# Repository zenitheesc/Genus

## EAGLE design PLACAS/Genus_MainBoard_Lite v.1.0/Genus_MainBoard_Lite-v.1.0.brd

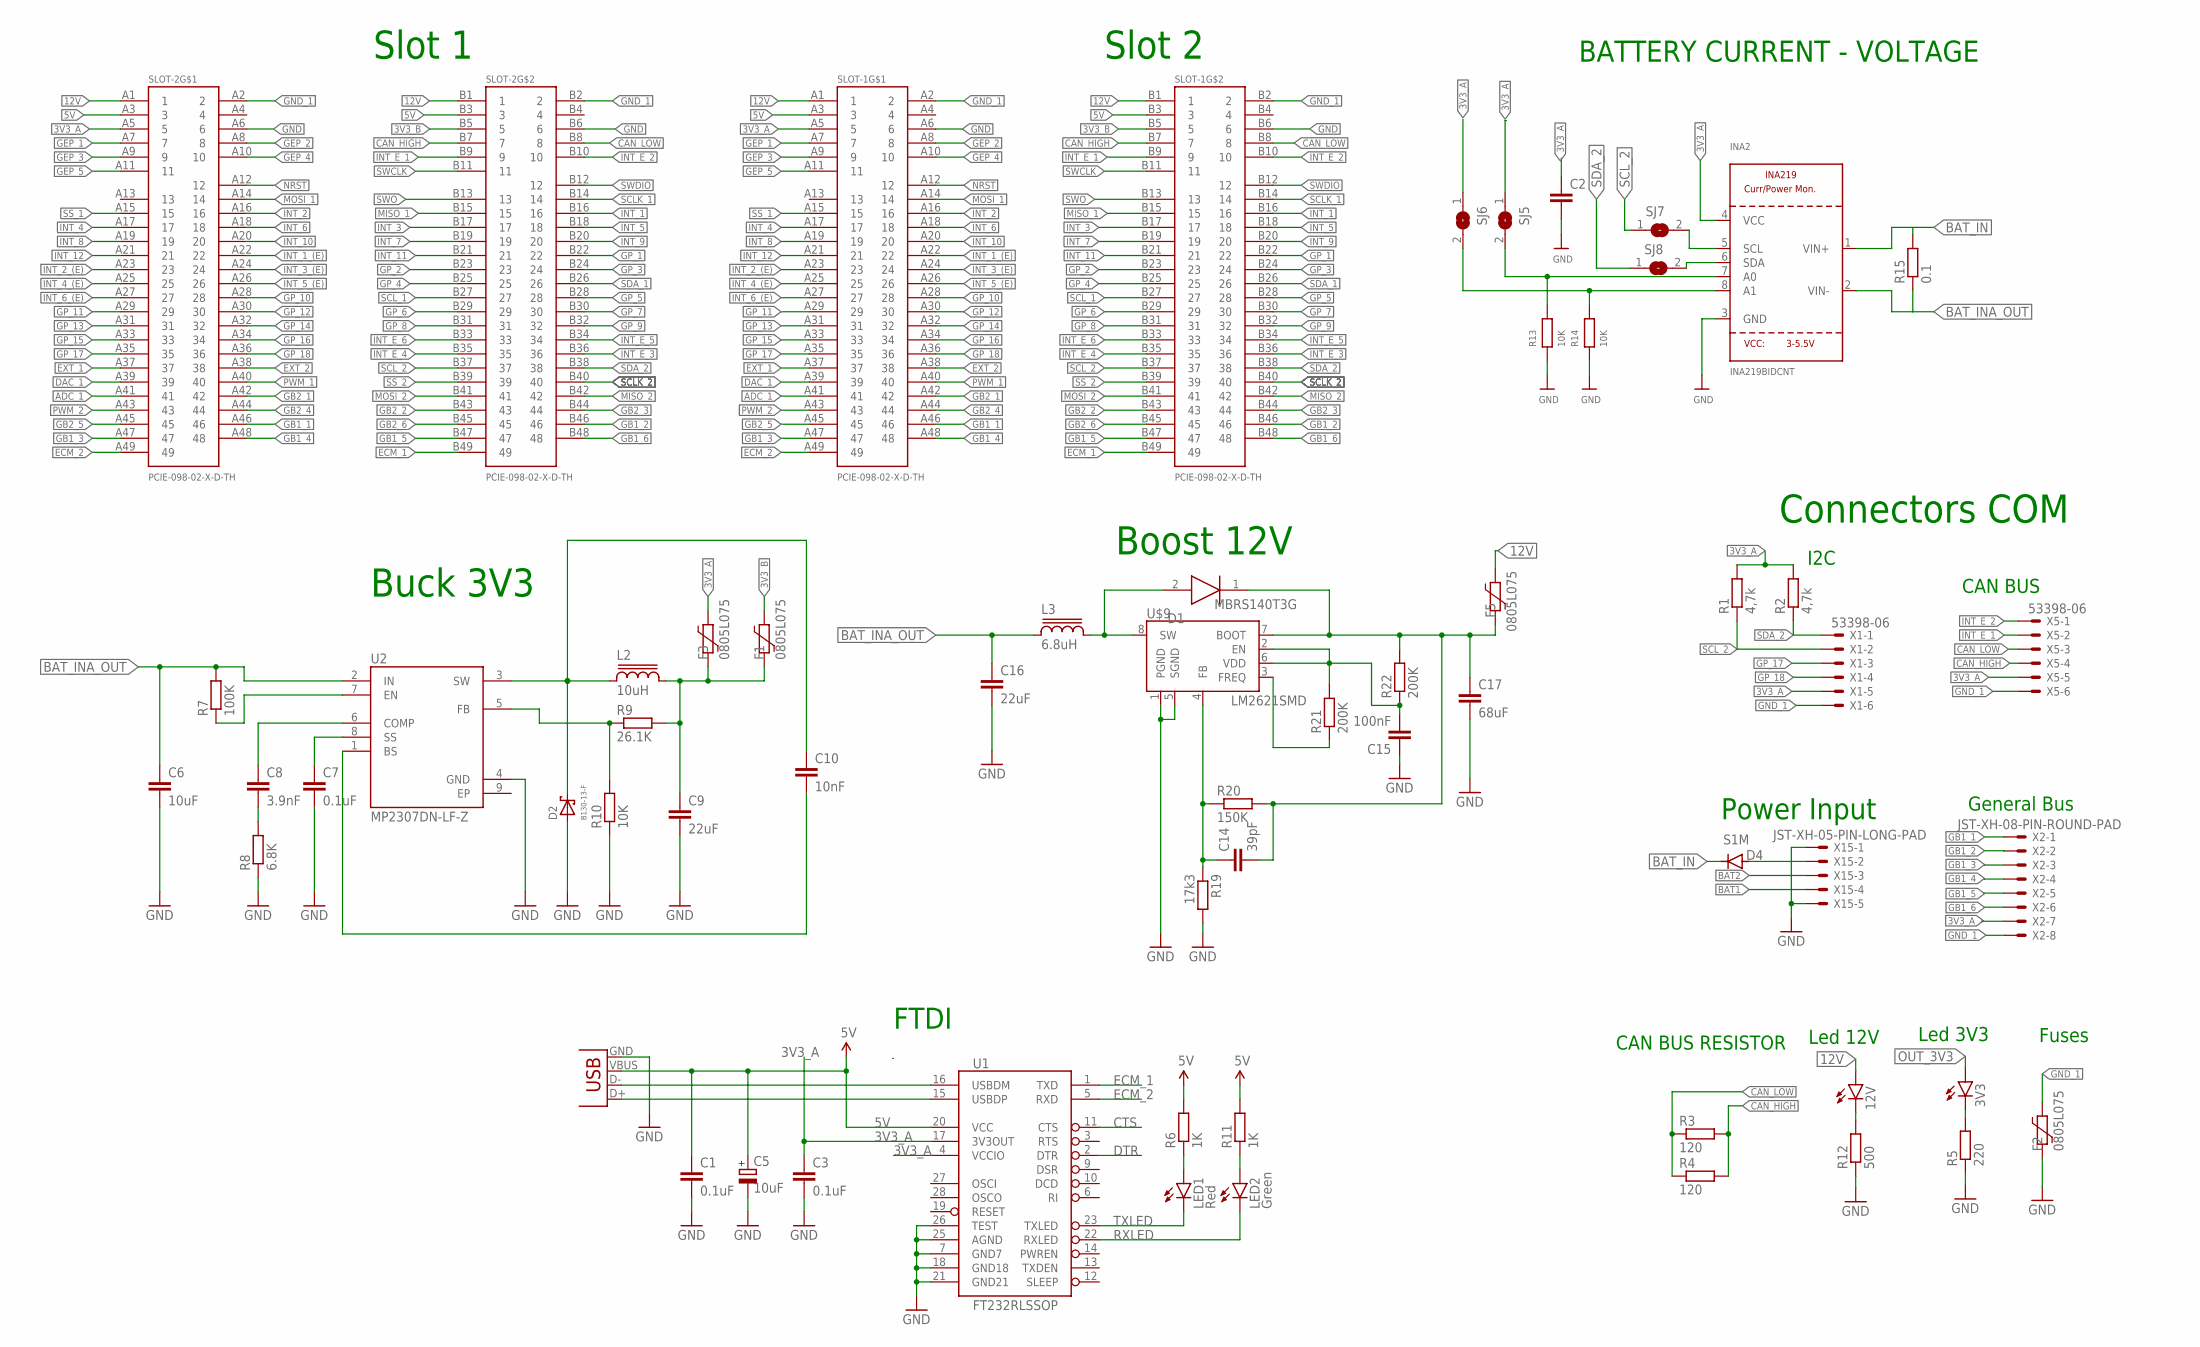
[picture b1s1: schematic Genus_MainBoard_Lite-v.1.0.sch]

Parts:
3V3, 12V: LEDCHIP-LED0805; CHIP-LED0805
C1, C3, C7: 0.1uF; C0805
C2: C-EUC0805; C0805
C5: 10uF; PANASONIC_B
C6: 10uF; C0805
C8: 3.9nF; C0805
C9: 22uF; C0805
C10: 10nF; C0805
C14: 39pF; C0805
C15: 100nF; C0805
C16: 22uF; C1210
C17: 68uF; C1210
D1: MBRS140T3G; DIOM5436X247N
D2: B130-13-F; SMA
D4: S1M; SMA
F1, F2, F3, F5: 0805L075; 0805L
INA2: INA219BIDCNT; SOT23-8
L2: 10uH; SRR1280
L3: 6.8uH; SRR1280
LED1: Red; CHIPLED_0805
LED2: Green; CHIPLED_0805
R1, R2: 4,7k; R0805
R3, R4: 120; R0805
R5: 220; R0805
R6, R11: 1K; R0805
R7: 100K; R0805
R8: 6.8K; R0805
R9: 26.1K; R0805
R10, R13, R14: 10K; R0805
R12: 500; R0805
R15: 0.1; R2512
R19: 17k3; R0805
R20: 150K; R0805
R21, R22: 200K; R0805
SJ5, SJ6, SJ7, SJ8: SOLDERJUMPERREFLOW_NOPASTE; SOLDERJUMPER_REFLOW_NOPASTE
SLOT-1, SLOT-2: PCIE-098-02-X-D-TH
U1: FT232RLSSOP; SSOP28DB
U2: MP2307DN-LF-Z; SOIC127P600X170-9N
U$9: LM2621SMD; MSOP-8
X1, X5: 53398-06
X2: JST-XH-08-PIN-ROUND-PAD; JST-XH-08-PACKAGE-ROUND-PAD
X3: USB-SMD-NS; USB-MINIB-NOSTOP
X15: JST-XH-05-PIN-LONG-PAD; JST-XH-05-PACKAGE-LONG-PAD

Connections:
3V3_A: C2.1, C3.1, F3.1, INA2.4 (VCC), R1.2, R2.2, SJ5.1, SJ6.1, SLOT-1.A5 (5), SLOT-2.A5 (5), U1.4 (VCCIO), U1.17 (3V3OUT), X1.5, X2.7, X5.5
3V3_B: F1.1, SLOT-1.B5 (5), SLOT-2.B5 (5)
5V: C1.1, C5.+, R6.2, R11.2, SLOT-1.A3 (3), SLOT-1.B3 (3), SLOT-2.A3 (3), SLOT-2.B3 (3), U1.20 (VCC), X3.VBUS
12V: 12V.A, F5.1, SLOT-1.A1 (1), SLOT-1.B1 (1), SLOT-2.A1 (1), SLOT-2.B1 (1)
ADC_1: SLOT-1.A41 (41), SLOT-2.A41 (41)
BAT1: X15.4
BAT2: X15.3
BAT_IN: D4.C, INA2.1 (VIN+), R15.2
BAT_INA_OUT: C6.1, C16.1, INA2.2 (VIN-), L3.1, R7.2, R15.1, U2.2 (IN)
CAN_HIGH: R3.2, R4.2, SLOT-1.B7 (7), SLOT-2.B7 (7), X5.4
CAN_LOW: R3.1, R4.1, SLOT-1.B8 (8), SLOT-2.B8 (8), X5.3
CTS: U1.11 (CTS)
DAC_1: SLOT-1.A39 (39), SLOT-2.A39 (39)
DTR: U1.2 (DTR)
ECM_1: SLOT-1.B49 (49), SLOT-2.B49 (49), U1.1 (TXD)
ECM_2: SLOT-1.A49 (49), SLOT-2.A49 (49), U1.5 (RXD)
EP: U2.9 (EP)
EXT_1: SLOT-1.A37 (37), SLOT-2.A37 (37)
EXT_2: SLOT-1.A38 (38), SLOT-2.A38 (38)
GB1_1: SLOT-1.A46 (46), SLOT-2.A46 (46), X2.1
GB1_2: SLOT-1.B46 (46), SLOT-2.B46 (46), X2.2
GB1_3: SLOT-1.A47 (47), SLOT-2.A47 (47), X2.3
GB1_4: SLOT-1.A48 (48), SLOT-2.A48 (48), X2.4
GB1_5: SLOT-1.B47 (47), SLOT-2.B47 (47), X2.5
GB1_6: SLOT-1.B48 (48), SLOT-2.B48 (48), X2.6
GB2_1: SLOT-1.A42 (42), SLOT-2.A42 (42)
GB2_2: SLOT-1.B43 (43), SLOT-2.B43 (43)
GB2_3: SLOT-1.B44 (44), SLOT-2.B44 (44)
GB2_4: SLOT-1.A44 (44), SLOT-2.A44 (44)
GB2_5: SLOT-1.A45 (45), SLOT-2.A45 (45)
GB2_6: SLOT-1.B45 (45), SLOT-2.B45 (45)
GEP_1: SLOT-1.A7 (7), SLOT-2.A7 (7)
GEP_2: SLOT-1.A8 (8), SLOT-2.A8 (8)
GEP_3: SLOT-1.A9 (9), SLOT-2.A9 (9)
GEP_4: SLOT-1.A10 (10), SLOT-2.A10 (10)
GEP_5: SLOT-1.A11 (11), SLOT-2.A11 (11)
GND: C1.2, C2.2, C3.2, C5.-, C6.2, C7.2, C9.2, C15.1, C16.2, C17.2, D2.A, F2.2, INA2.3 (GND), R5.1, R8.1, R10.1, R12.1, R13.1, R14.1, R19.2, SLOT-1.A6 (6), SLOT-1.B6 (6), SLOT-2.A6 (6), SLOT-2.B6 (6), U1.7 (GND7), U1.18 (GND18), U1.21 (GND21), U1.25 (AGND), U1.26 (TEST), U2.4 (GND), U$9.1 (PGND), U$9.5 (SGND), X3.GND, X15.1, X15.5
GND_1: F2.1, SLOT-1.A2 (2), SLOT-1.B2 (2), SLOT-2.A2 (2), SLOT-2.B2 (2), X1.6, X2.8, X5.6
GP_1: SLOT-1.B22 (22), SLOT-2.B22 (22)
GP_2: SLOT-1.B23 (23), SLOT-2.B23 (23)
GP_3: SLOT-1.B24 (24), SLOT-2.B24 (24)
GP_4: SLOT-1.B25 (25), SLOT-2.B25 (25)
GP_5: SLOT-1.B28 (28), SLOT-2.B28 (28)
GP_6: SLOT-1.B29 (29), SLOT-2.B29 (29)
GP_7: SLOT-1.B30 (30), SLOT-2.B30 (30)
GP_8: SLOT-1.B31 (31), SLOT-2.B31 (31)
GP_9: SLOT-1.B32 (32), SLOT-2.B32 (32)
GP_10: SLOT-1.A28 (28), SLOT-2.A28 (28)
GP_11: SLOT-1.A29 (29), SLOT-2.A29 (29)
GP_12: SLOT-1.A30 (30), SLOT-2.A30 (30)
GP_13: SLOT-1.A31 (31), SLOT-2.A31 (31)
GP_14: SLOT-1.A32 (32), SLOT-2.A32 (32)
GP_15: SLOT-1.A33 (33), SLOT-2.A33 (33)
GP_16: SLOT-1.A34 (34), SLOT-2.A34 (34)
GP_17: SLOT-1.A35 (35), SLOT-2.A35 (35), X1.3
GP_18: SLOT-1.A36 (36), SLOT-2.A36 (36), X1.4
INT_1: SLOT-1.B16 (16), SLOT-2.B16 (16)
INT_1_(E): SLOT-1.A22 (22), SLOT-2.A22 (22)
INT_2: SLOT-1.A16 (16), SLOT-2.A16 (16)
INT_2_(E): SLOT-1.A23 (23), SLOT-2.A23 (23)
INT_3: SLOT-1.B17 (17), SLOT-2.B17 (17)
INT_3_(E): SLOT-1.A24 (24), SLOT-2.A24 (24)
INT_4: SLOT-1.A17 (17), SLOT-2.A17 (17)
INT_4_(E): SLOT-1.A25 (25), SLOT-2.A25 (25)
INT_5: SLOT-1.B18 (18), SLOT-2.B18 (18)
INT_5_(E): SLOT-1.A26 (26), SLOT-2.A26 (26)
INT_6: SLOT-1.A18 (18), SLOT-2.A18 (18)
INT_6_(E): SLOT-1.A27 (27), SLOT-2.A27 (27)
INT_7: SLOT-1.B19 (19), SLOT-2.B19 (19)
INT_8: SLOT-1.A19 (19), SLOT-2.A19 (19)
INT_9: SLOT-1.B20 (20), SLOT-2.B20 (20)
INT_10: SLOT-1.A20 (20), SLOT-2.A20 (20)
INT_11: SLOT-1.B21 (21), SLOT-2.B21 (21)
INT_12: SLOT-1.A21 (21), SLOT-2.A21 (21)
INT_E_1: SLOT-1.B9 (9), SLOT-2.B9 (9), X5.2
INT_E_2: SLOT-1.B10 (10), SLOT-2.B10 (10), X5.1
INT_E_3: SLOT-1.B36 (36), SLOT-2.B36 (36)
INT_E_4: SLOT-1.B35 (35), SLOT-2.B35 (35)
INT_E_5: SLOT-1.B34 (34), SLOT-2.B34 (34)
INT_E_6: SLOT-1.B33 (33), SLOT-2.B33 (33)
MISO_1: SLOT-1.B15 (15), SLOT-2.B15 (15)
MISO_2: SLOT-1.B42 (42), SLOT-2.B42 (42)
MOSI_1: SLOT-1.A14 (14), SLOT-2.A14 (14)
MOSI_2: SLOT-1.B41 (41), SLOT-2.B41 (41)
unnamed: LED1.A, R6.1
unnamed: LED2.A, R11.1
unnamed: 12V.C, R12.2
unnamed: INA2.8 (A1), R14.2, SJ6.2
unnamed: D4.A, X15.2
unnamed: INA2.7 (A0), R13.2, SJ5.2
unnamed: R7.1, U2.7 (EN)
unnamed: C8.2, R8.2
unnamed: C7.1, U2.8 (SS)
unnamed: C8.1, U2.6 (COMP)
unnamed: C10.1, D2.C, L2.1, U2.3 (SW)
unnamed: R9.1, R10.2, U2.5 (FB)
unnamed: C10.2, U2.1 (BS)
unnamed: INA2.5 (SCL), SJ7.2
unnamed: INA2.6 (SDA), SJ8.2
unnamed: C14.1, R19.1, R20.1, U$9.4 (FB)
unnamed: D1.2 (A), L3.2, U$9.8 (SW)
unnamed: C15.2, R21.2, R22.1, U$9.2 (EN), U$9.6 (VDD)
unnamed: R21.1, U$9.3 (FREQ)
unnamed: 3V3.C, R5.2
NRST: SLOT-1.A12 (12), SLOT-2.A12 (12)
OUT: C14.2, C17.1, D1.1 (K), F5.2, R20.2, R22.2, U$9.7 (BOOT)
OUT_3V3: 3V3.A, C9.1, F1.2, F3.2, L2.2, R9.2
PWM_1: SLOT-1.A40 (40), SLOT-2.A40 (40)
PWM_2: SLOT-1.A43 (43), SLOT-2.A43 (43)
RXLED: LED2.C, U1.22 (RXLED)
SCLK_1: SLOT-1.B14 (14), SLOT-2.B14 (14)
SCLK_2: SLOT-1.B40 (40), SLOT-2.B40 (40)
SCL_1: SLOT-1.B27 (27), SLOT-2.B27 (27)
SCL_2: R1.1, SJ7.1, SLOT-1.B37 (37), SLOT-2.B37 (37), X1.2
SDA_1: SLOT-1.B26 (26), SLOT-2.B26 (26)
SDA_2: R2.1, SJ8.1, SLOT-1.B38 (38), SLOT-2.B38 (38), X1.1
SS_1: SLOT-1.A15 (15), SLOT-2.A15 (15)
SS_2: SLOT-1.B39 (39), SLOT-2.B39 (39)
SWCLK: SLOT-1.B11 (11), SLOT-2.B11 (11)
SWDIO: SLOT-1.B12 (12), SLOT-2.B12 (12)
SWO: SLOT-1.B13 (13), SLOT-2.B13 (13)
TXLED: LED1.C, U1.23 (TXLED)
USB_D+: U1.15 (USBDP), X3.D+
USB_D-: U1.16 (USBDM), X3.D-

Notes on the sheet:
Slot 1
Slot 2
CAN BUS
I2C
Power Input
Buck 3V3
Connectors COM
CAN BUS RESISTOR
Led 3V3
BATTERY CURRENT - VOLTAGE
Fuses
General Bus
FTDI
Boost 12V
Led 12V

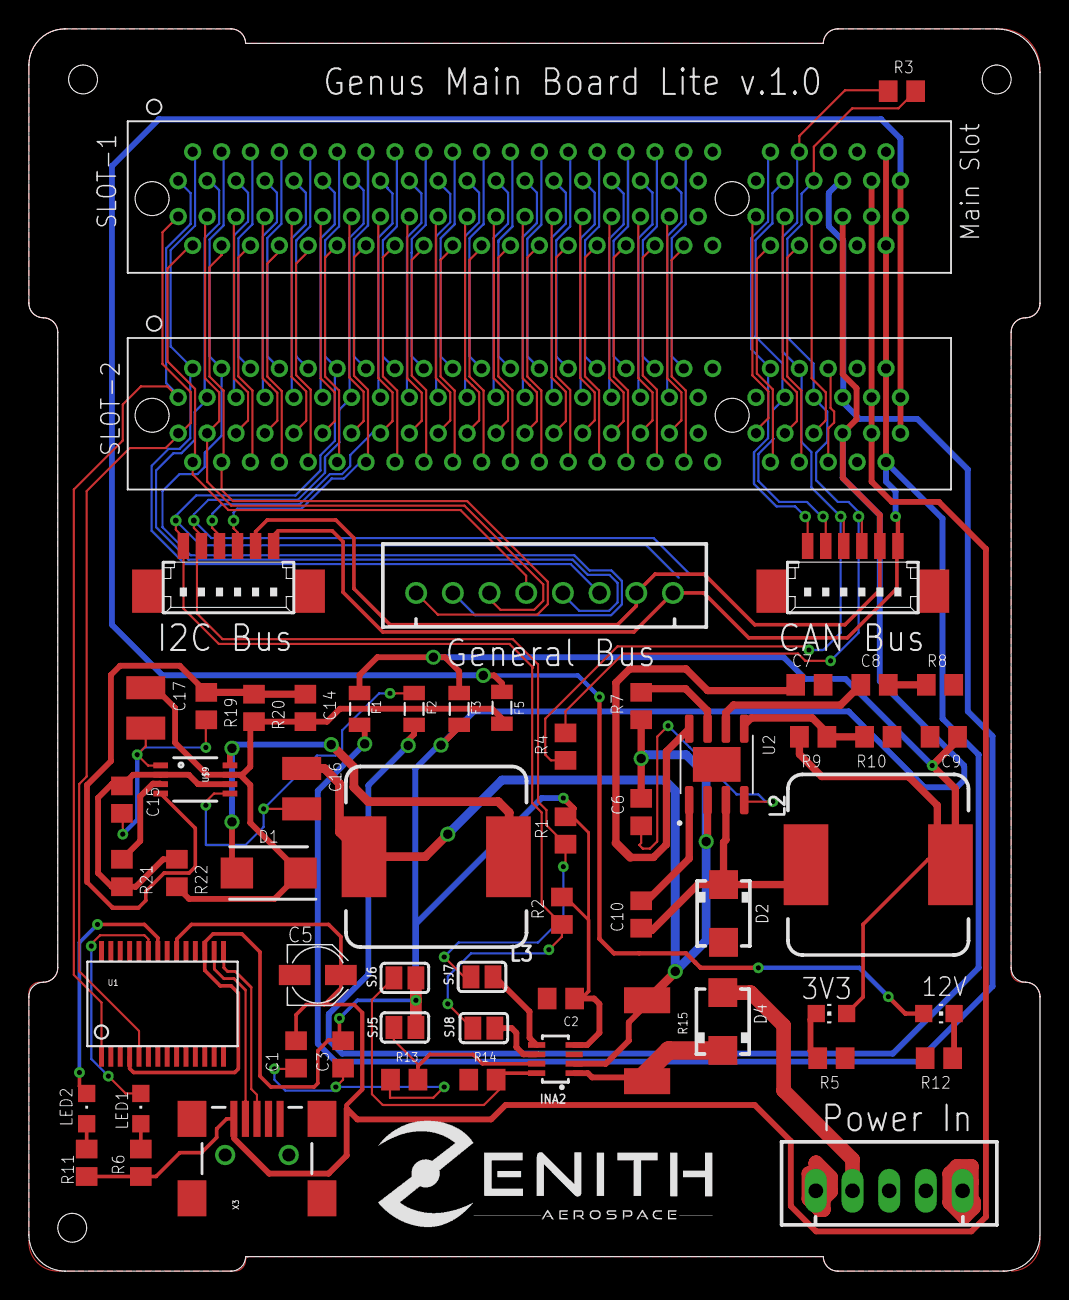
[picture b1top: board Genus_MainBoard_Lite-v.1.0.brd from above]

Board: 2 copper layers, 70.0 x 86.0 mm, 60 parts (0 on the bottom side), 119 nets.

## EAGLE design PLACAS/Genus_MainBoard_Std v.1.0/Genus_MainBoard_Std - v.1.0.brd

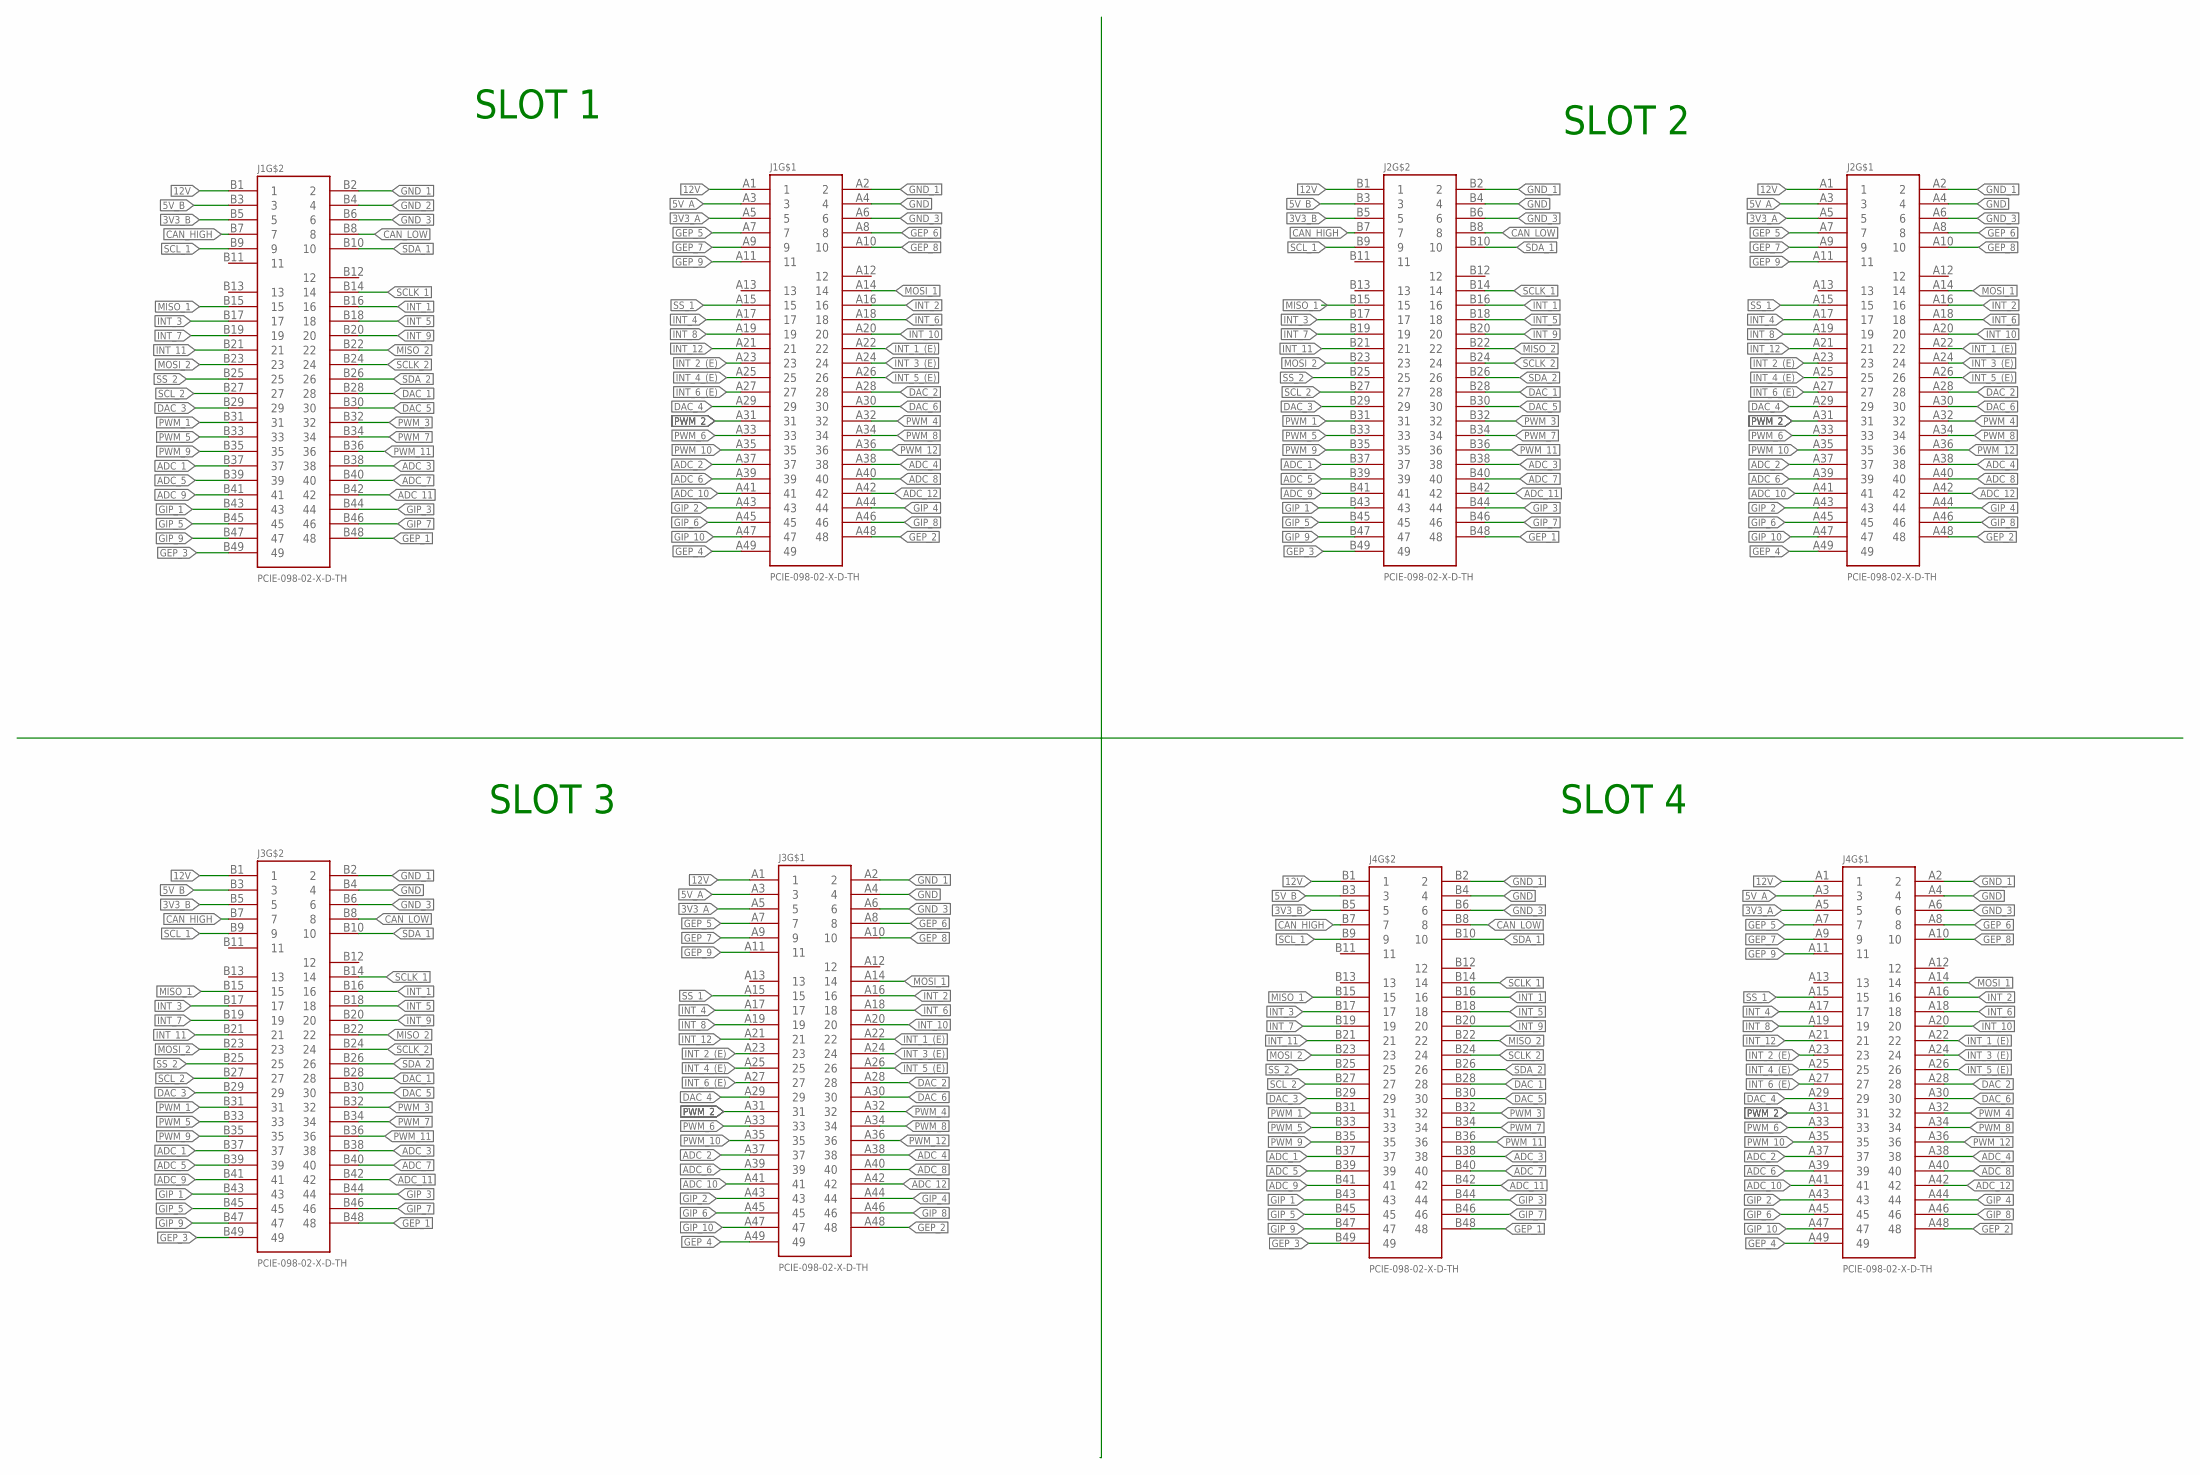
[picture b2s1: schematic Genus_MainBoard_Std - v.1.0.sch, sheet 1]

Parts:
J1, J2, J3, J4: PCIE-098-02-X-D-TH

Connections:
unnamed: J1.A1 (1), J1.B1 (1), J2.A1 (1), J2.B1 (1), J3.A1 (1), J3.B1 (1), J4.A1 (1), J4.B1 (1)
unnamed: J1.A2 (2), J1.B2 (2), J2.A2 (2), J2.B2 (2), J3.A2 (2), J3.B2 (2), J4.A2 (2), J4.B2 (2)
unnamed: J1.A3 (3), J2.A3 (3), J3.A3 (3), J4.A3 (3)
unnamed: J1.A4 (4), J2.A4 (4), J2.B4 (4), J3.A4 (4), J3.B4 (4), J4.A4 (4), J4.B4 (4)
unnamed: J1.A5 (5), J2.A5 (5), J3.A5 (5), J4.A5 (5)
unnamed: J1.A6 (6), J1.B6 (6), J2.A6 (6), J2.B6 (6), J3.A6 (6), J3.B6 (6), J4.A6 (6), J4.B6 (6)
unnamed: J1.A7 (7), J2.A7 (7), J3.A7 (7), J4.A7 (7)
unnamed: J1.A8 (8), J2.A8 (8), J3.A8 (8), J4.A8 (8)
unnamed: J1.A9 (9), J2.A9 (9), J3.A9 (9), J4.A9 (9)
unnamed: J1.A10 (10), J2.A10 (10), J3.A10 (10), J4.A10 (10)
unnamed: J1.A11 (11), J2.A11 (11), J3.A11 (11), J4.A11 (11)
unnamed: J1.A14 (14), J2.A14 (14), J3.A14 (14), J4.A14 (14)
unnamed: J1.A15 (15), J2.A15 (15), J3.A15 (15), J4.A15 (15)
unnamed: J1.A16 (16), J2.A16 (16), J3.A16 (16), J4.A16 (16)
unnamed: J1.A17 (17), J2.A17 (17), J3.A17 (17), J4.A17 (17)
unnamed: J1.A18 (18), J2.A18 (18), J3.A18 (18), J4.A18 (18)
unnamed: J1.A19 (19), J2.A19 (19), J3.A19 (19), J4.A19 (19)
unnamed: J1.A20 (20), J2.A20 (20), J3.A20 (20), J4.A20 (20)
unnamed: J1.A21 (21), J2.A21 (21), J3.A21 (21), J4.A21 (21)
unnamed: J1.A22 (22), J2.A22 (22), J3.A22 (22), J4.A22 (22)
unnamed: J1.A23 (23), J2.A23 (23), J3.A23 (23), J4.A23 (23)
unnamed: J1.A24 (24), J2.A24 (24), J3.A24 (24), J4.A24 (24)
unnamed: J1.A25 (25), J2.A25 (25), J3.A25 (25), J4.A25 (25)
unnamed: J1.A26 (26), J2.A26 (26), J3.A26 (26), J4.A26 (26)
unnamed: J1.A27 (27), J2.A27 (27), J3.A27 (27), J4.A27 (27)
unnamed: J1.A28 (28), J2.A28 (28), J3.A28 (28), J4.A28 (28)
unnamed: J1.A29 (29), J2.A29 (29), J3.A29 (29), J4.A29 (29)
unnamed: J1.A30 (30), J2.A30 (30), J3.A30 (30), J4.A30 (30)
unnamed: J1.A31 (31), J2.A31 (31), J3.A31 (31), J4.A31 (31)
unnamed: J1.A32 (32), J2.A32 (32), J3.A32 (32), J4.A32 (32)
unnamed: J1.A33 (33), J2.A33 (33), J3.A33 (33), J4.A33 (33)
unnamed: J1.A34 (34), J2.A34 (34), J3.A34 (34), J4.A34 (34)
unnamed: J1.A35 (35), J2.A35 (35), J3.A35 (35), J4.A35 (35)
unnamed: J1.A36 (36), J2.A36 (36), J3.A36 (36), J4.A36 (36)
unnamed: J1.A37 (37), J2.A37 (37), J3.A37 (37), J4.A37 (37)
unnamed: J1.A38 (38), J2.A38 (38), J3.A38 (38), J4.A38 (38)
unnamed: J1.A39 (39), J2.A39 (39), J3.A39 (39), J4.A39 (39)
unnamed: J1.A40 (40), J2.A40 (40), J3.A40 (40), J4.A40 (40)
unnamed: J1.A41 (41), J2.A41 (41), J3.A41 (41), J4.A41 (41)
unnamed: J1.A42 (42), J2.A42 (42), J3.A42 (42), J4.A42 (42)
unnamed: J1.A43 (43), J2.A43 (43), J3.A43 (43), J4.A43 (43)
unnamed: J1.A44 (44), J2.A44 (44), J3.A44 (44), J4.A44 (44)
unnamed: J1.A45 (45), J2.A45 (45), J3.A45 (45), J4.A45 (45)
unnamed: J1.A46 (46), J2.A46 (46), J3.A46 (46), J4.A46 (46)
unnamed: J1.A47 (47), J2.A47 (47), J3.A47 (47), J4.A47 (47)
unnamed: J1.A48 (48), J2.A48 (48), J3.A48 (48), J4.A48 (48)
unnamed: J1.A49 (49), J2.A49 (49), J3.A49 (49), J4.A49 (49)
unnamed: J1.B3 (3), J2.B3 (3), J3.B3 (3), J4.B3 (3)
unnamed: J1.B5 (5), J2.B5 (5), J3.B5 (5), J4.B5 (5)
unnamed: J1.B7 (7), J2.B7 (7), J3.B7 (7), J4.B7 (7)
unnamed: J1.B8 (8), J2.B8 (8), J3.B8 (8), J4.B8 (8)
unnamed: J1.B9 (9), J2.B9 (9), J3.B9 (9), J4.B9 (9)
unnamed: J1.B10 (10), J2.B10 (10), J3.B10 (10), J4.B10 (10)
unnamed: J1.B14 (14), J2.B14 (14), J3.B14 (14), J4.B14 (14)
unnamed: J1.B15 (15), J2.B15 (15), J3.B15 (15), J4.B15 (15)
unnamed: J1.B16 (16), J2.B16 (16), J3.B16 (16), J4.B16 (16)
unnamed: J1.B17 (17), J2.B17 (17), J3.B17 (17), J4.B17 (17)
unnamed: J1.B18 (18), J2.B18 (18), J3.B18 (18), J4.B18 (18)
unnamed: J1.B19 (19), J2.B19 (19), J3.B19 (19), J4.B19 (19)
unnamed: J1.B20 (20), J2.B20 (20), J3.B20 (20), J4.B20 (20)
unnamed: J1.B21 (21), J2.B21 (21), J3.B21 (21), J4.B21 (21)
unnamed: J1.B22 (22), J2.B22 (22), J3.B22 (22), J4.B22 (22)
unnamed: J1.B23 (23), J2.B23 (23), J3.B23 (23), J4.B23 (23)
unnamed: J1.B24 (24), J2.B24 (24), J3.B24 (24), J4.B24 (24)
unnamed: J1.B25 (25), J2.B25 (25), J3.B25 (25), J4.B25 (25)
unnamed: J1.B26 (26), J2.B26 (26), J3.B26 (26), J4.B26 (26)
unnamed: J1.B27 (27), J2.B27 (27), J3.B27 (27), J4.B27 (27)
unnamed: J1.B28 (28), J2.B28 (28), J3.B28 (28), J4.B28 (28)
unnamed: J1.B29 (29), J2.B29 (29), J3.B29 (29), J4.B29 (29)
unnamed: J1.B30 (30), J2.B30 (30), J3.B30 (30), J4.B30 (30)
unnamed: J1.B31 (31), J2.B31 (31), J3.B31 (31), J4.B31 (31)
unnamed: J1.B32 (32), J2.B32 (32), J3.B32 (32), J4.B32 (32)
unnamed: J1.B33 (33), J2.B33 (33), J3.B33 (33), J4.B33 (33)
unnamed: J1.B34 (34), J2.B34 (34), J3.B34 (34), J4.B34 (34)
unnamed: J1.B35 (35), J2.B35 (35), J3.B35 (35), J4.B35 (35)
unnamed: J1.B36 (36), J2.B36 (36), J3.B36 (36), J4.B36 (36)
unnamed: J1.B37 (37), J2.B37 (37), J3.B37 (37), J4.B37 (37)
unnamed: J1.B38 (38), J2.B38 (38), J3.B38 (38), J4.B38 (38)
unnamed: J1.B39 (39), J2.B39 (39), J3.B39 (39), J4.B39 (39)
unnamed: J1.B40 (40), J2.B40 (40), J3.B40 (40), J4.B40 (40)
unnamed: J1.B41 (41), J2.B41 (41), J3.B41 (41), J4.B41 (41)
unnamed: J1.B42 (42), J2.B42 (42), J3.B42 (42), J4.B42 (42)
unnamed: J1.B43 (43), J2.B43 (43), J3.B43 (43), J4.B43 (43)
unnamed: J1.B44 (44), J2.B44 (44), J3.B44 (44), J4.B44 (44)
unnamed: J1.B45 (45), J2.B45 (45), J3.B45 (45), J4.B45 (45)
unnamed: J1.B46 (46), J2.B46 (46), J3.B46 (46), J4.B46 (46)
unnamed: J1.B47 (47), J2.B47 (47), J3.B47 (47), J4.B47 (47)
unnamed: J1.B48 (48), J2.B48 (48), J3.B48 (48), J4.B48 (48)
unnamed: J1.B49 (49), J2.B49 (49), J3.B49 (49), J4.B49 (49)

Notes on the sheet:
SLOT 1
SLOT 2
SLOT 3
SLOT 4

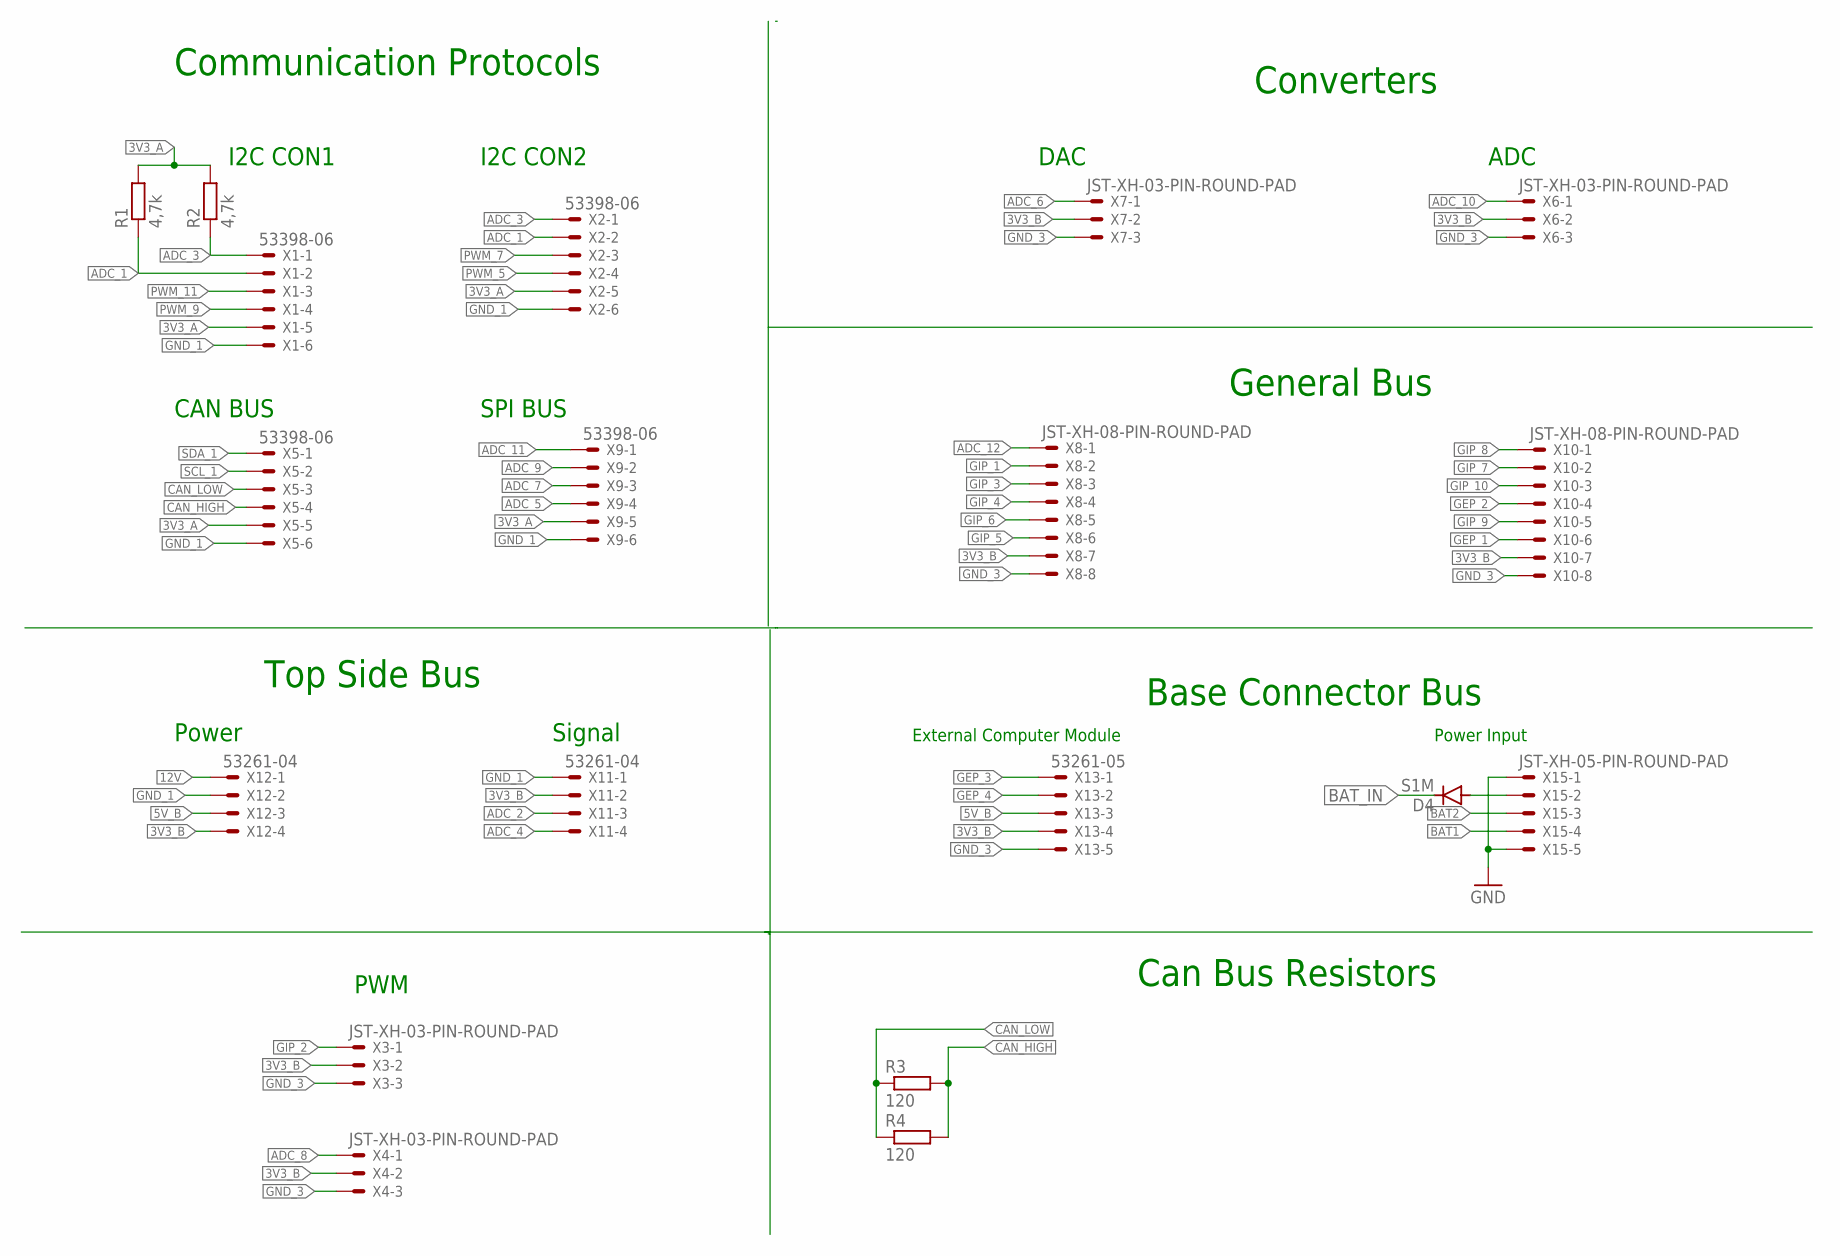
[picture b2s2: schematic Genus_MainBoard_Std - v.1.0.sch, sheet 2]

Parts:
D4: S1M; SMA
R1, R2: 4,7k; R0805
R3, R4: 120; R0805
X1, X2, X5, X9: 53398-06
X3, X4, X6, X7: JST-XH-03-PIN-ROUND-PAD; JST-XH-03-PACKAGE-ROUND-PAD
X8, X10: JST-XH-08-PIN-ROUND-PAD; JST-XH-08-PACKAGE-ROUND-PAD
X11, X12: 53261-04
X13: 53261-05
X15: JST-XH-05-PIN-ROUND-PAD; JST-XH-05-PACKAGE-ROUND-PAD

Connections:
3V3_A: R1.2, R2.2, X1.5, X2.5, X5.5, X9.5; also elsewhere on the board
3V3_B: X3.2, X4.2, X6.2, X7.2, X8.7, X10.7, X11.2, X12.4, X13.4; also elsewhere on the board
5V_B: X12.3, X13.3; also elsewhere on the board
12V: X12.1; also elsewhere on the board
ADC_1: R1.1, X1.2, X2.2; also elsewhere on the board
ADC_2: X11.3; also elsewhere on the board
ADC_3: R2.1, X1.1, X2.1; also elsewhere on the board
ADC_4: X11.4; also elsewhere on the board
ADC_5: X9.4; also elsewhere on the board
ADC_6: X7.1; also elsewhere on the board
ADC_7: X9.3; also elsewhere on the board
ADC_8: X4.1; also elsewhere on the board
ADC_9: X9.2; also elsewhere on the board
ADC_10: X6.1; also elsewhere on the board
ADC_11: X9.1; also elsewhere on the board
ADC_12: X8.1; also elsewhere on the board
BAT1: X15.4
BAT2: X15.3
BAT_IN: D4.C; also elsewhere on the board
CAN_HIGH: R3.2, R4.2, X5.4; also elsewhere on the board
CAN_LOW: R3.1, R4.1, X5.3; also elsewhere on the board
GEP_1: X10.6; also elsewhere on the board
GEP_2: X10.4; also elsewhere on the board
GEP_3: X13.1; also elsewhere on the board
GEP_4: X13.2; also elsewhere on the board
GIP_1: X8.2; also elsewhere on the board
GIP_2: X3.1; also elsewhere on the board
GIP_3: X8.3; also elsewhere on the board
GIP_4: X8.4; also elsewhere on the board
GIP_5: X8.6; also elsewhere on the board
GIP_6: X8.5; also elsewhere on the board
GIP_7: X10.2; also elsewhere on the board
GIP_8: X10.1; also elsewhere on the board
GIP_9: X10.5; also elsewhere on the board
GIP_10: X10.3; also elsewhere on the board
GND: X15.1, X15.5; also elsewhere on the board
GND_1: X1.6, X2.6, X5.6, X9.6, X11.1, X12.2; also elsewhere on the board
GND_3: X3.3, X4.3, X6.3, X7.3, X8.8, X10.8, X13.5; also elsewhere on the board
unnamed: D4.A, X15.2
PWM_5: X2.4; also elsewhere on the board
PWM_7: X2.3; also elsewhere on the board
PWM_9: X1.4; also elsewhere on the board
PWM_11: X1.3; also elsewhere on the board
SCL_1: X5.2; also elsewhere on the board
SDA_1: X5.1; also elsewhere on the board

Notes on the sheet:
CAN BUS
PWM
ADC
Power
Signal
I2C CON1
SPI BUS
I2C CON2
Communication Protocols
General Bus
DAC
Converters
Top Side Bus
Base Connector Bus
Can Bus Resistors
External Computer Module
Power Input

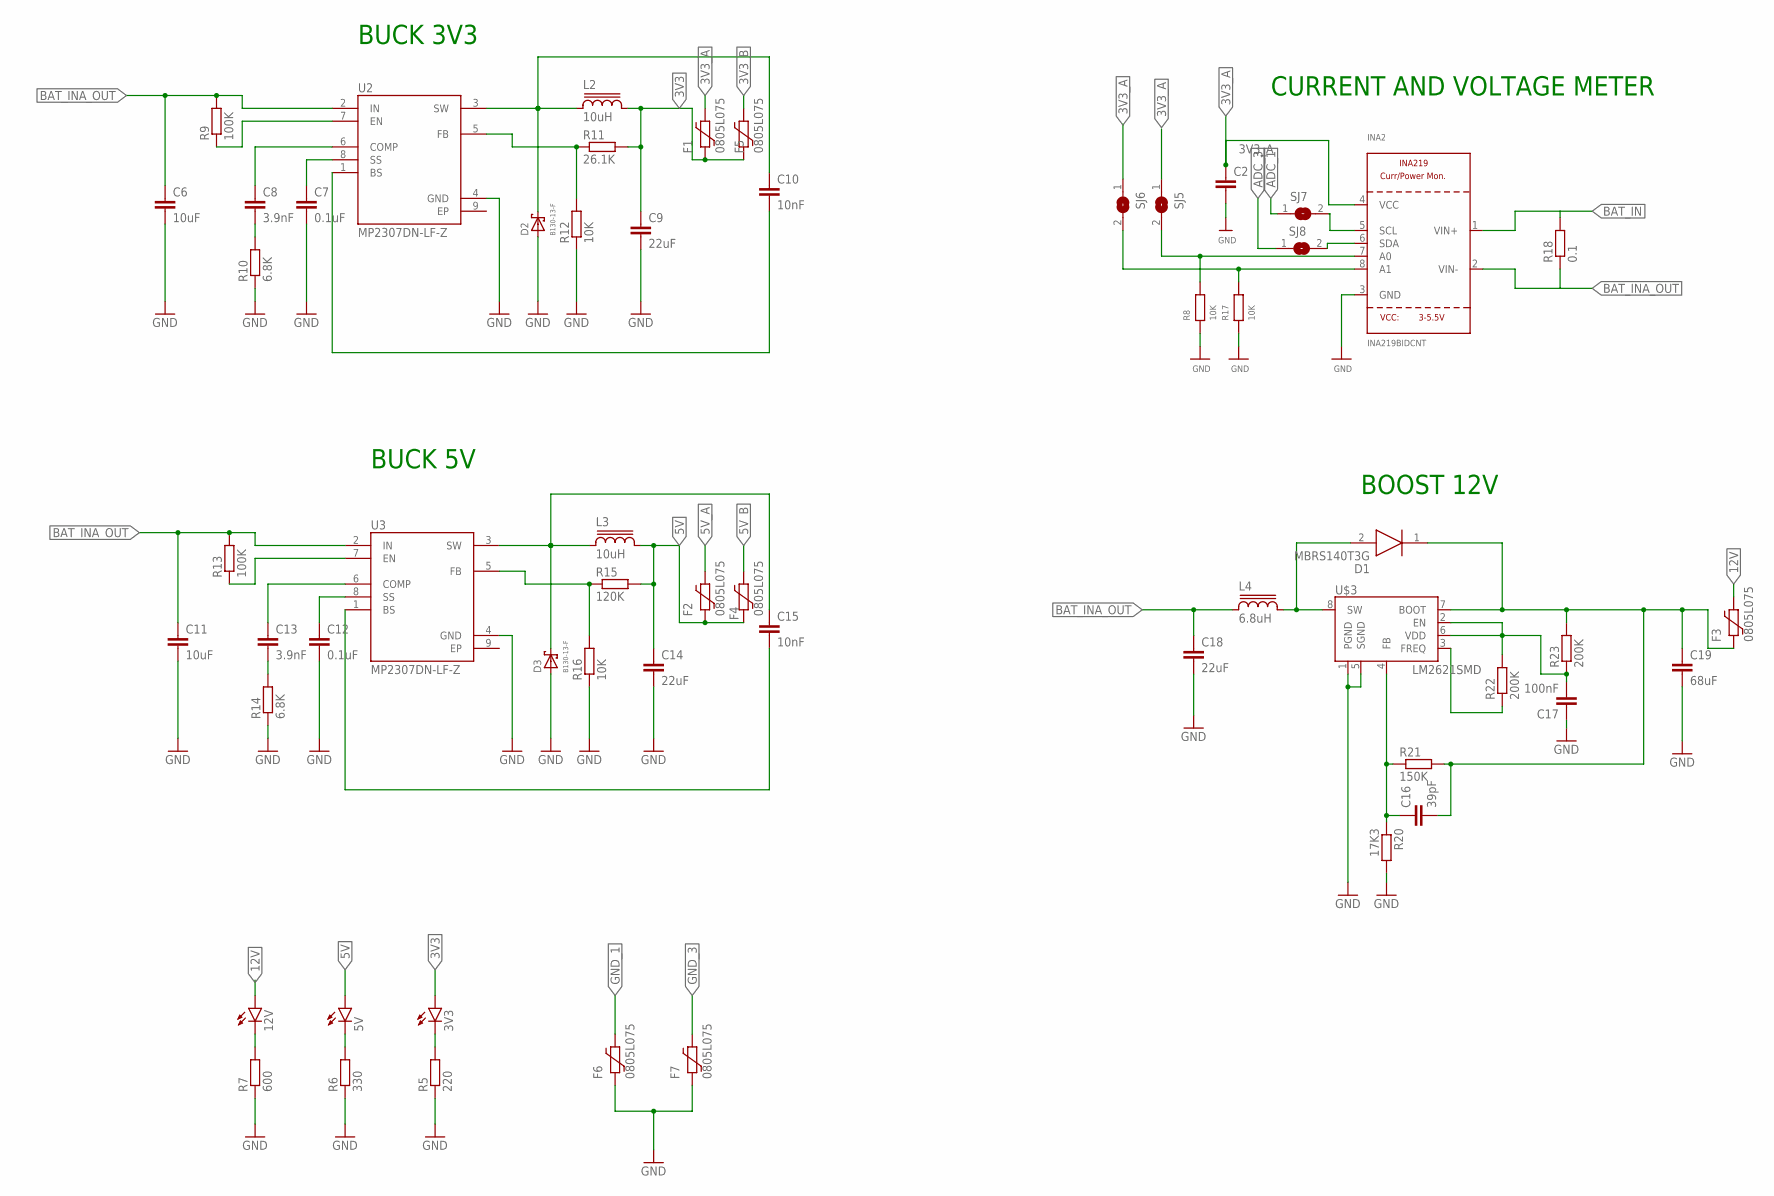
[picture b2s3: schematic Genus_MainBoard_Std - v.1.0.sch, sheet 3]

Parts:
3V3, 5V, 12V: LEDCHIP-LED0805; CHIP-LED0805
C2: C-EUC0805; C0805
C6, C11: 10uF; C0805
C7, C12: 0.1uF; C0805
C8, C13: 3.9nF; C0805
C9, C14: 22uF; C0805
C10, C15: 10nF; C0805
C16: 39pF; C0805
C17: 100nF; C0805
C18: 22uF; C1210
C19: 68uF; C1210
D1: MBRS140T3G; DIOM5436X247N
D2, D3: B130-13-F; SMA
F1, F2, F3, F4, F5, F6, F7: 0805L075; 0805L
INA2: INA219BIDCNT; SOT23-8
L2, L3: 10uH; SRR1280
L4: 6.8uH; SRR1280
R5: 220; R0805
R6: 330; R0805
R7: 600; R0805
R8, R12, R16, R17: 10K; R0805
R9, R13: 100K; R0805
R10, R14: 6.8K; R0805
R11: 26.1K; R0805
R15: 120K; R0805
R18: 0.1; R2512
R20: 17K3; R0805
R21: 150K; R0805
R22, R23: 200K; R0805
SJ5, SJ6, SJ7, SJ8: SOLDERJUMPERREFLOW_NOPASTE; SOLDERJUMPER_REFLOW_NOPASTE
U2, U3: MP2307DN-LF-Z; SOIC127P600X170-9N
U$3: LM2621SMD; MSOP-8

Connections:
3V3: 3V3.A, C9.1, F1.2, F5.2, L2.2, R11.2
3V3_A: C2.1, F1.1, INA2.4 (VCC), SJ5.1, SJ6.1; also elsewhere on the board
3V3_B: F5.1; also elsewhere on the board
5V: 5V.A, C14.1, F2.2, F4.2, L3.2, R15.2
5V_A: F2.1; also elsewhere on the board
5V_B: F4.1; also elsewhere on the board
12V: 12V.A, F3.1; also elsewhere on the board
ADC_1: SJ7.1; also elsewhere on the board
ADC_3: SJ8.1; also elsewhere on the board
BAT_IN: INA2.1 (VIN+), R18.2; also elsewhere on the board
BAT_INA_OUT: C6.1, C11.1, C18.1, INA2.2 (VIN-), L4.1, R9.2, R13.2, R18.1, U2.2 (IN), U3.2 (IN)
EP: U2.9 (EP), U3.9 (EP)
GND: C2.2, C6.2, C7.2, C9.2, C11.2, C12.2, C14.2, C17.1, C18.2, C19.2, D2.A, D3.A, F6.2, F7.2, INA2.3 (GND), R5.1, R6.1, R7.1, R8.1, R10.1, R12.1, R14.1, R16.1, R17.1, R20.2, U2.4 (GND), U3.4 (GND), U$3.1 (PGND), U$3.5 (SGND); also elsewhere on the board
GND_1: F6.1; also elsewhere on the board
GND_3: F7.1; also elsewhere on the board
unnamed: C16.2, C19.1, D1.1 (K), F3.2, R21.2, R23.2, U$3.7 (BOOT)
unnamed: 12V.C, R7.2
unnamed: INA2.8 (A1), R17.2, SJ6.2
unnamed: INA2.7 (A0), R8.2, SJ5.2
unnamed: INA2.5 (SCL), SJ7.2
unnamed: R9.1, U2.7 (EN)
unnamed: C8.2, R10.2
unnamed: C7.1, U2.8 (SS)
unnamed: C8.1, U2.6 (COMP)
unnamed: C10.1, D2.C, L2.1, U2.3 (SW)
unnamed: R11.1, R12.2, U2.5 (FB)
unnamed: C10.2, U2.1 (BS)
unnamed: R13.1, U3.7 (EN)
unnamed: C13.2, R14.2
unnamed: C12.1, U3.8 (SS)
unnamed: C13.1, U3.6 (COMP)
unnamed: C15.1, D3.C, L3.1, U3.3 (SW)
unnamed: R15.1, R16.2, U3.5 (FB)
unnamed: C15.2, U3.1 (BS)
unnamed: INA2.6 (SDA), SJ8.2
unnamed: C16.1, R20.1, R21.1, U$3.4 (FB)
unnamed: D1.2 (A), L4.2, U$3.8 (SW)
unnamed: C17.2, R22.2, R23.1, U$3.2 (EN), U$3.6 (VDD)
unnamed: R22.1, U$3.3 (FREQ)
unnamed: 5V.C, R6.2
unnamed: 3V3.C, R5.2

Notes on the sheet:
BUCK 3V3
BUCK 5V
BOOST 12V
CURRENT AND VOLTAGE METER

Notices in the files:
parts and their libraries:
inductor-bourns: Copyright (C) 2008, Bob Starr
SparkFun-PowerIC: Licensing: Creative Commons ShareAlike 4.0 International - https://creativecommons.org/licenses/by-sa/4.0
